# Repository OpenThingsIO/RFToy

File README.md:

This folder contains RFToy hardware design files, firmware code, and documents.

RFToy 1.0/1.1 are based on ATmega328.
RFToy 3.0/3.1 are based on ESP8266.

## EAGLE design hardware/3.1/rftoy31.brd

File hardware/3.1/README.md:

RFToy 3.1 is completely re-designed from RFToy 3.0. It no longer uses the OpenSprinkler top-layer board. Instead, RFToy 3.1 has its own compact circuit, with all features from RFToy 3.0 but additionally the capability of receiving/sending IR (infared) signals, and a dedicated 3D printed enclosure.

The power circuit has been simplified from the previous version, in that the AMS1117-33 linear voltage regulator has been replaced by two series LL4148 diodes, dropping about 1.6V from the 5V input, resulting in 3.3~3.4V VCC voltage for ESP8266. Also, the auto-reset circuit for CH340 has been simplified by removing two MMBT3904 NPN transistors and their base resistors. This works because both CH340 and ESP8266 use the same VCC voltage, hence no level shifting is needed.

The GPIO pin assignments are printed on the bottom layer silkscreen of the circuit board.

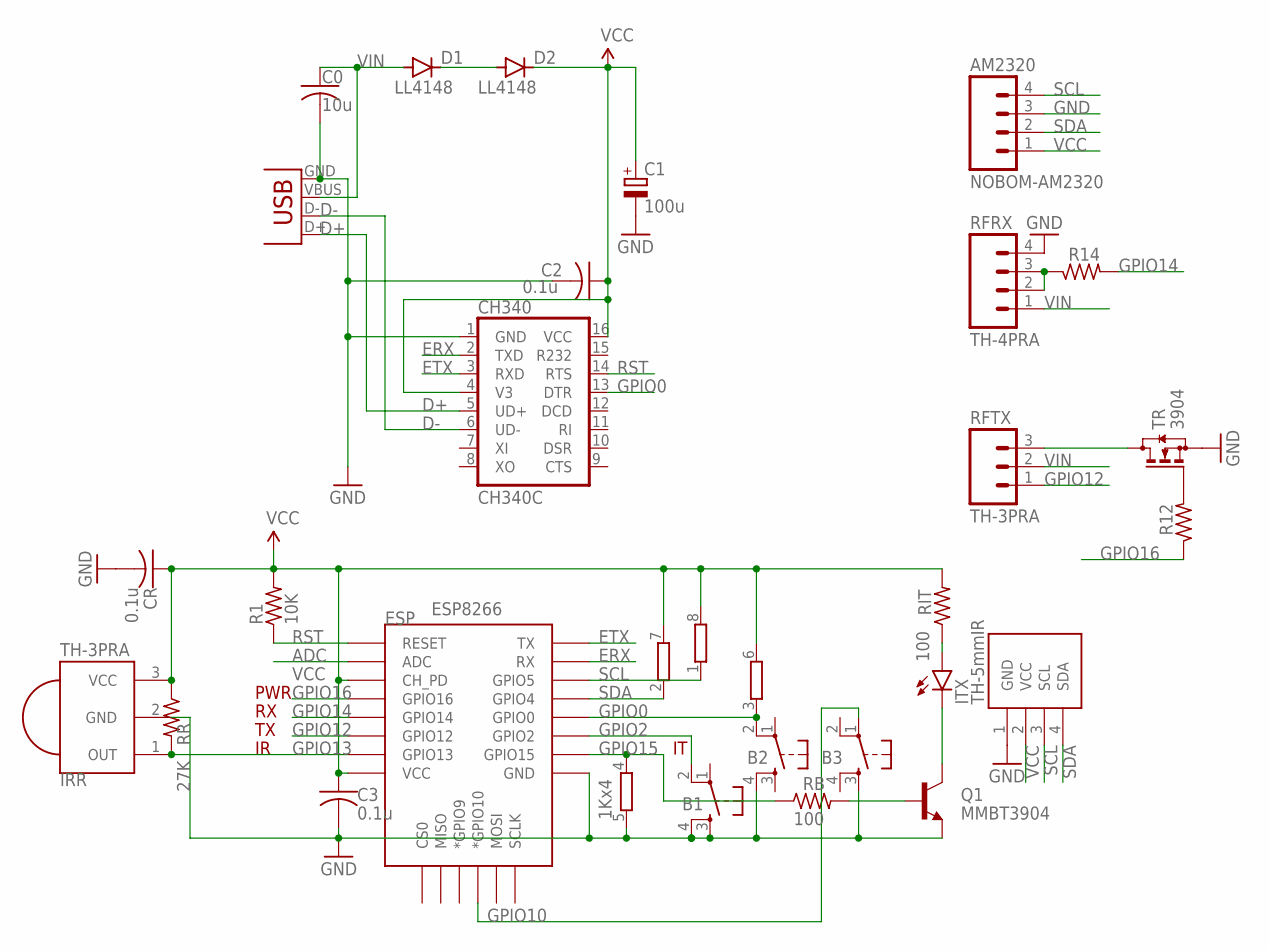
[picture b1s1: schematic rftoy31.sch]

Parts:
AM2320: NOBOM-AM2320; 1X04_NO_SILK
B1, B2, B3: TH-TACT6x9; EVQ-Q2-SMD
C0: 10u; C0805K
C1: 100u; PANASONIC_C
C2: 0.1u; C0603K
C3: 0.1u; C0603
CH340: CH340C; SO16
CR: 0.1u; C0603
D1, D2: LL4148; MINIMELF
ESP: ESP8266; ESP12E-SMD
IRR: TH-3PRA; PNA460XM
ITX: TH-5mmIR; IRL80A
LCD: NOBOM-OLED; SSD1306_OLED_I2C_PCB_0.75_B
Q1: MMBT3904; SOT23
R1: 10K; R0603
R12, R14: 1K; R0603
RB: 100; R0603
RFRX: TH-4PRA; 1X04_LONGPADS
RFTX: TH-3PRA; 1X03_NO_SILK
RIT: 100; R0603
RN1: 1Kx4; EXB38V
RR: 27K; R0603
TR: 3904; SOT23
X3: USBMICROB2; USB-MICROB2

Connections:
ADC: ESP.ADC
D+: CH340.5 (UD+), X3.D+
D-: CH340.6 (UD-), X3.D-
ERX: CH340.2 (TXD), ESP.RXD0 (RX)
ETX: CH340.3 (RXD), ESP.TXD0 (TX)
GND: AM2320.3, B1.3, B1.4, B2.4, B3.3, C0.2, C1.-, C2.2, C3.2, CH340.1 (GND), CR.2, ESP.GND, IRR.2 (GND), LCD.1 (GND), Q1.2 (E), RFRX.4, RN1.5 (2), TR.2 (S), X3.GND
GPIO0: B2.2, CH340.13 (DTR), ESP.GPIO0, RN1.3 (1)
GPIO2: B1.2, ESP.GPIO2
GPIO10: B3.1, ESP.GPIO10 (*GPIO10)
GPIO12: ESP.GPIO12, RFTX.1
GPIO13: ESP.GPIO13, IRR.1 (OUT), RR.2
GPIO14: ESP.GPIO14, R14.2
GPIO15: ESP.GPIO15, RB.1, RN1.4 (1)
GPIO16: ESP.GPIO16, R12.1
unnamed: D1.C, D2.A
unnamed: ITX.K (C), Q1.3 (C)
unnamed: Q1.1 (B), RB.2
unnamed: R12.2, TR.1 (G)
unnamed: ITX.A, RIT.1
unnamed: R14.1, RFRX.2, RFRX.3
unnamed: RFTX.3, TR.3 (D)
RST: CH340.14 (RTS), ESP.RESET, R1.1
SCL: AM2320.4, ESP.GPIO5, LCD.3 (SCL), RN1.1
SDA: AM2320.2, ESP.GPIO4, LCD.4 (SDA), RN1.2 (1)
VCC: AM2320.1, C1.+, C2.1, C3.1, CH340.4 (V3), CH340.16 (VCC), CR.1, D2.C, ESP.CH_PD, ESP.VCC, IRR.3 (VCC), LCD.2 (VCC), R1.2, RIT.2, RN1.6 (2), RN1.7 (2), RN1.8 (2), RR.1
VIN: C0.1, D1.A, RFRX.1, RFTX.2, X3.VBUS

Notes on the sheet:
PWR

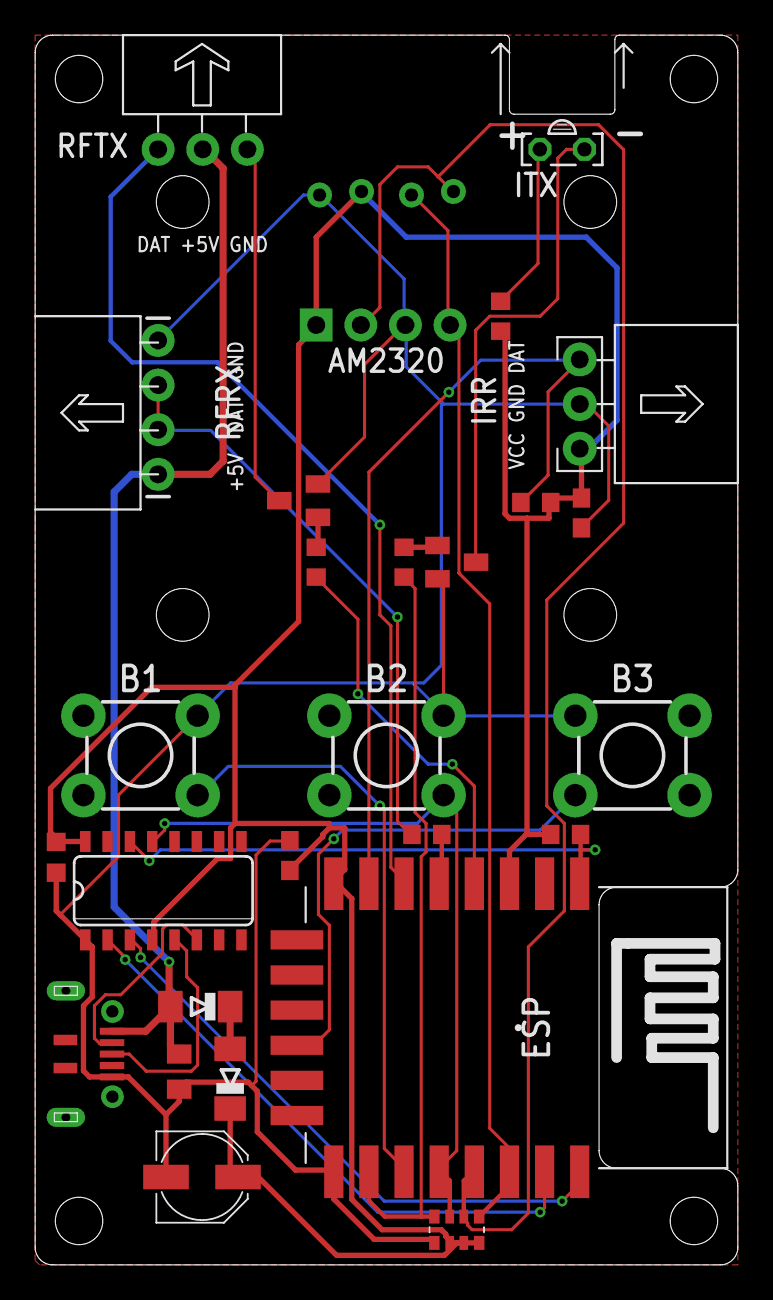
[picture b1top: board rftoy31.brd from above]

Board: 2 copper layers, 40.0 x 70.0 mm, 28 parts (0 on the bottom side), 25 nets.

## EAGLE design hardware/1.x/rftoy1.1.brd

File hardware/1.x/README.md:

RFToy 1.0/1.1 schematic and board design files.

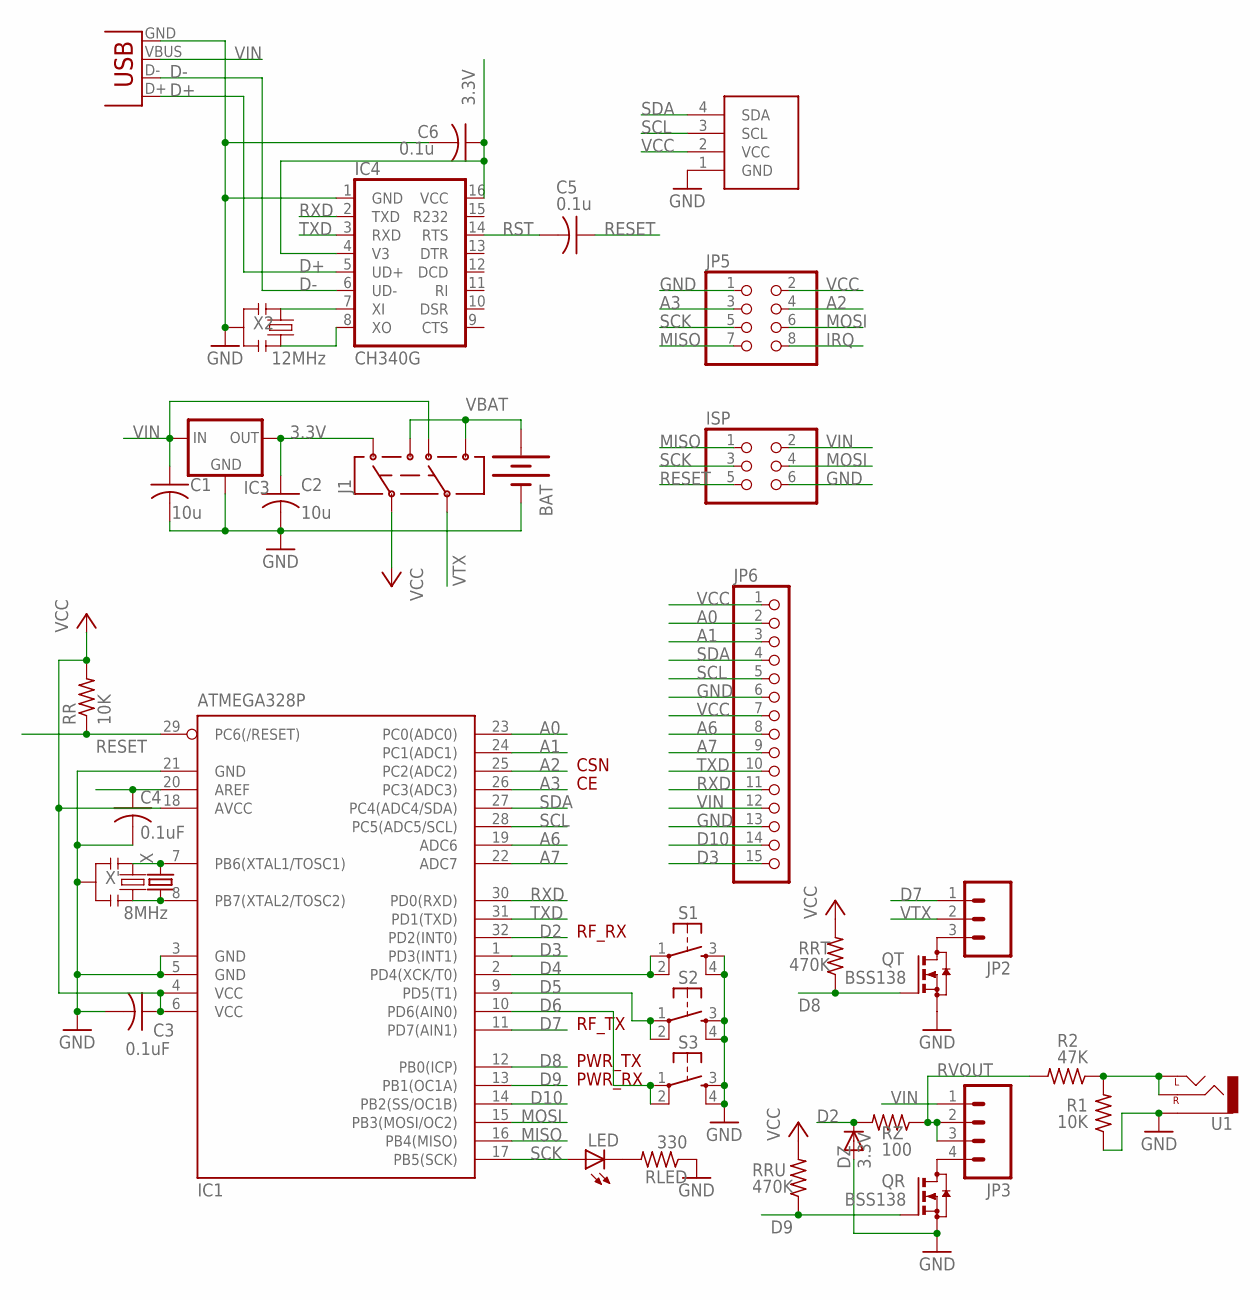
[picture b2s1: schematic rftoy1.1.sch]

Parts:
BAT: BATTERY20PTH; BATTCOM_20MM_PTH
C1, C2: 10u; C0805K
C3, C4: 0.1uF; C0603K
C5, C6: 0.1u; C0603K
DZ: 3.3V; MINIMELF
IC1: ATMEGA328P; TQFP32-08
IC3: MCP1700SOT233; SOT23
IC4: CH340G; SO16
ISP: PINHD-2X3; 2X03
J1: AYZ0202
JP2: M03LOCK_LONGPADS; 1X03_LOCK_LONGPADS
JP3: M04LOCK; 1X04_LOCK
JP5: PINHD-2X4; 2X04
JP6: PINHD-1X15-CB; 1X15-CB
LED: LEDCHIPLED_0805; CHIPLED_0805
QR: BSS138; SOT23
QT: BSS138; SOT23
R1: 10K; R0805
R2: 47K; R0805
RLED: 330; R0805
RR: 10K; R0805
RRT: 470K; R0805
RRU: 470K; R0805
RZ: 100; R0805
S1, S2, S3: TAC_SWITCHPTH; TACTILE-PTH
U1: AUDIO-JACKSMD3; AUDIO-JACK-3.5MM-SMD3
U$1: SSD1306_OLED_I2C
X: CRYSTALTC26V; TC26V
X1: USBSMD; USB-MINIB
X2: 12MHz; RESONATOR-SMD
X': 8MHz; RESONATOR-SMD

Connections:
3.3V: C2.1, C6.1, IC3.2 (OUT), IC4.4 (V3), IC4.16 (VCC), J1.3 (1)
A0: IC1.23 (PC0(ADC0)), JP6.2
A1: IC1.24 (PC1(ADC1)), JP6.3
A2: IC1.25 (PC2(ADC2)), JP5.4
A3: IC1.26 (PC3(ADC3)), JP5.3
A6: IC1.19 (ADC6), JP6.8
A7: IC1.22 (ADC7), JP6.9
AREF: C4.1, IC1.20 (AREF)
D2: DZ.C, IC1.32 (PD2(INT0)), RZ.2
D3: IC1.1 (PD3(INT1)), JP6.15
D4: IC1.2 (PD4(XCK/T0)), S1.1, S1.2
D5: IC1.9 (PD5(T1)), S2.1, S2.2
D6: IC1.10 (PD6(AIN0)), S3.1, S3.2
D7: IC1.11 (PD7(AIN1)), JP2.1
D8: IC1.12 (PB0(ICP)), QT.1 (G), RRT.1
D9: IC1.13 (PB1(OC1A)), QR.1 (G), RRU.1
D10: IC1.14 (PB2(SS/OC1B)), JP6.14
D+: IC4.5 (UD+), X1.D+
D-: IC4.6 (UD-), X1.D-
GND: BAT.2 (-), C1.2, C2.2, C3.2, C4.2, C6.2, DZ.A, IC1.3 (GND), IC1.5 (GND), IC1.21 (GND), IC3.1 (GND), IC4.1 (GND), ISP.6, JP5.1, JP6.6, JP6.13, QR.2 (S), QT.2 (S), R1.1, RLED.1, S1.3, S1.4, S2.3, S2.4, S3.3, S3.4, U1.RING (SLEEVE), U$1.1 (GND), X1.GND, X2.2, X'.2
IRQ: JP5.8
MISO: IC1.16 (PB4(MISO)), ISP.1, JP5.7
MOSI: IC1.15 (PB3(MOSI/OC2)), ISP.4, JP5.6
unnamed: LED.C, RLED.2
unnamed: IC1.7 (PB6(XTAL1/TOSC1)), X.2, X'.1
unnamed: IC1.8 (PB7(XTAL2/TOSC2)), X.1, X'.3
unnamed: R1.2, R2.1, U1.MID (RIGHT), U1.TIP (LEFT)
unnamed: JP3.4, QR.3 (D)
unnamed: JP2.3, QT.3 (D)
unnamed: IC4.7 (XI), X2.1
unnamed: IC4.8 (XO), X2.3
RESET: C5.1, IC1.29 (PC6(/RESET)), ISP.5, RR.1
RST: C5.2, IC4.14 (RTS)
RVOUT: JP3.2, JP3.3, R2.2, RZ.1
RXD: IC1.30 (PD0(RXD)), IC4.2 (TXD), JP6.11
SCK: IC1.17 (PB5(SCK)), ISP.3, JP5.5, LED.A
SCL: IC1.28 (PC5(ADC5/SCL)), JP6.5, U$1.3 (SCL)
SDA: IC1.27 (PC4(ADC4/SDA)), JP6.4, U$1.4 (SDA)
TXD: IC1.31 (PD1(TXD)), IC4.3 (RXD), JP6.10
VBAT: BAT.1 (+), J1.1 (3), J1.4 (6)
VCC: C3.1, IC1.4 (VCC), IC1.6 (VCC), IC1.18 (AVCC), J1.2, JP5.2, JP6.1, JP6.7, RR.2, RRT.2, RRU.2, U$1.2 (VCC)
VIN: C1.1, IC3.3 (IN), ISP.2, J1.6 (4), JP3.1, JP6.12, X1.VBUS
VTX: J1.5, JP2.2

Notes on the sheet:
RF_RX
PWR_RX
PWR_TX
RF_TX
CSN

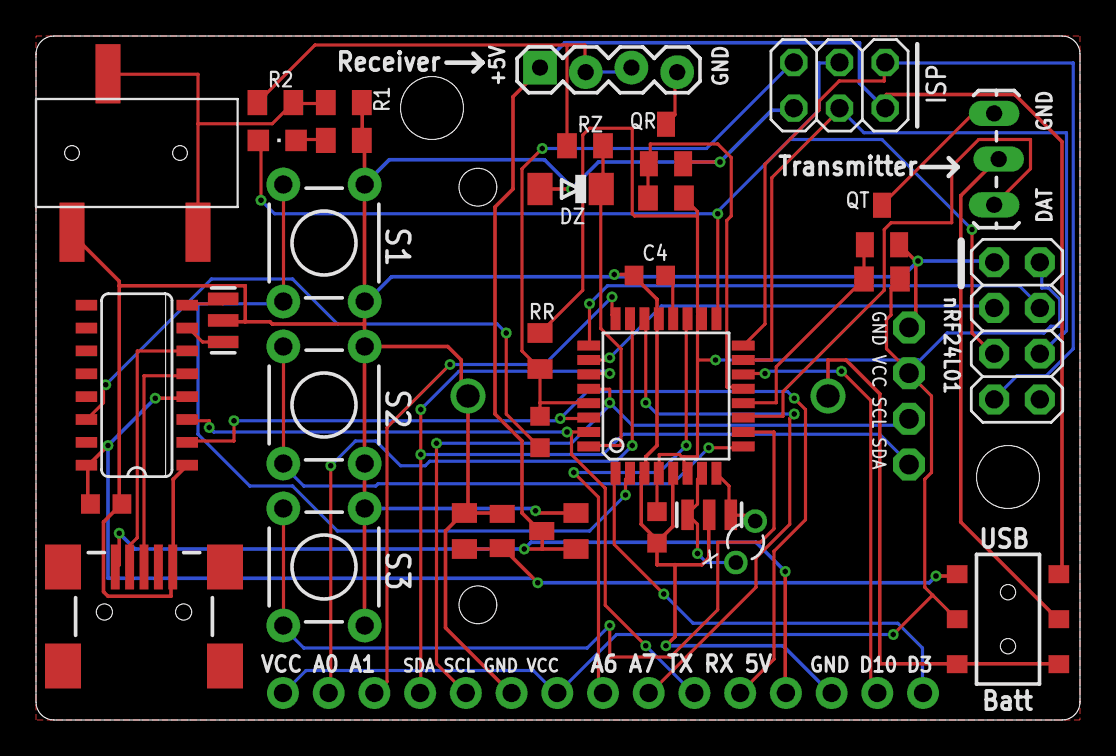
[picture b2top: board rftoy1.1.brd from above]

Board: 2 copper layers, 58.0 x 38.0 mm, 36 parts (1 on the bottom side), 42 nets.

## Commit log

2018-03-06 check in firmware for rftoy3.0
2018-03-06 add readme and older files
2018-03-29 Add WPS config option on startup
2021-10-29 add hardware 3.1 design files; firmware 3.1; update documents
2021-10-29 move classic version user manual to archived
2024-08-06 modify firmware to support general protocols and bit lenghts
2024-08-06 add version code prefix
2024-08-07 change font for better display

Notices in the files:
parts and their libraries:
SparkFunNew: Licensing: CC v3.0 Share-Alike You are welcome to use this library for commercial purposes.
